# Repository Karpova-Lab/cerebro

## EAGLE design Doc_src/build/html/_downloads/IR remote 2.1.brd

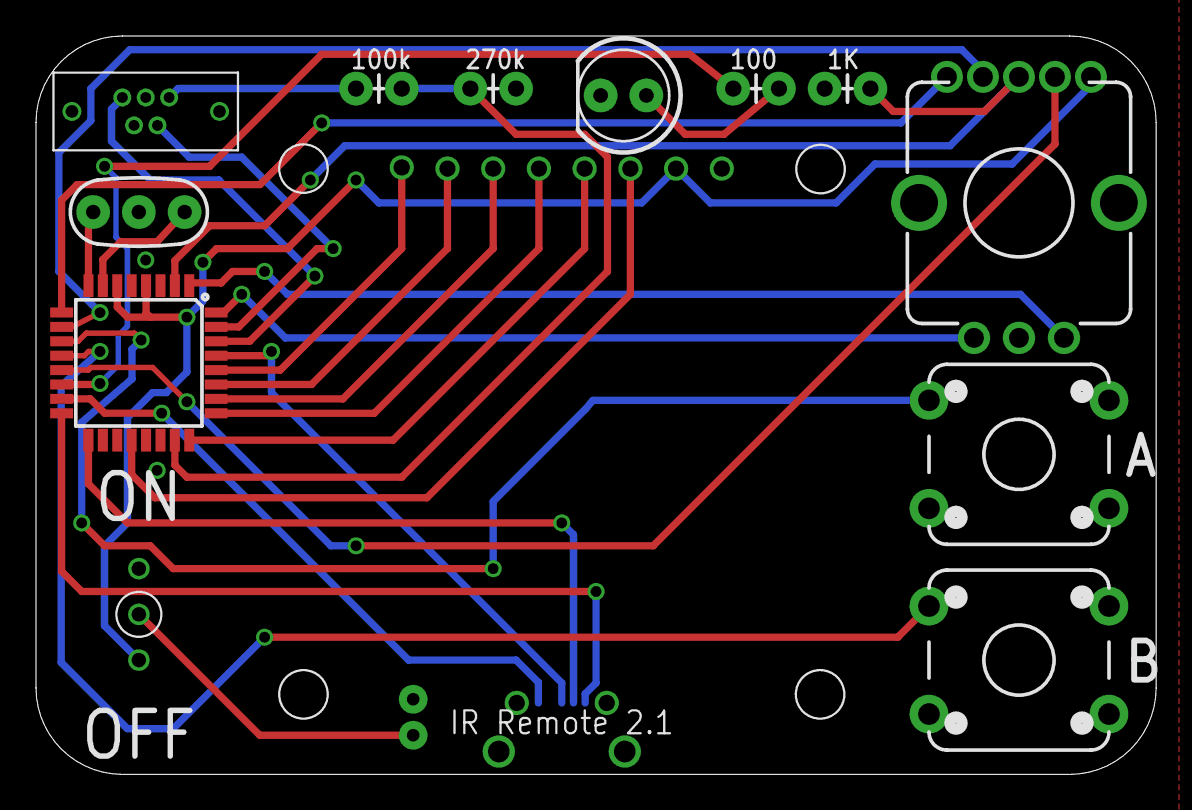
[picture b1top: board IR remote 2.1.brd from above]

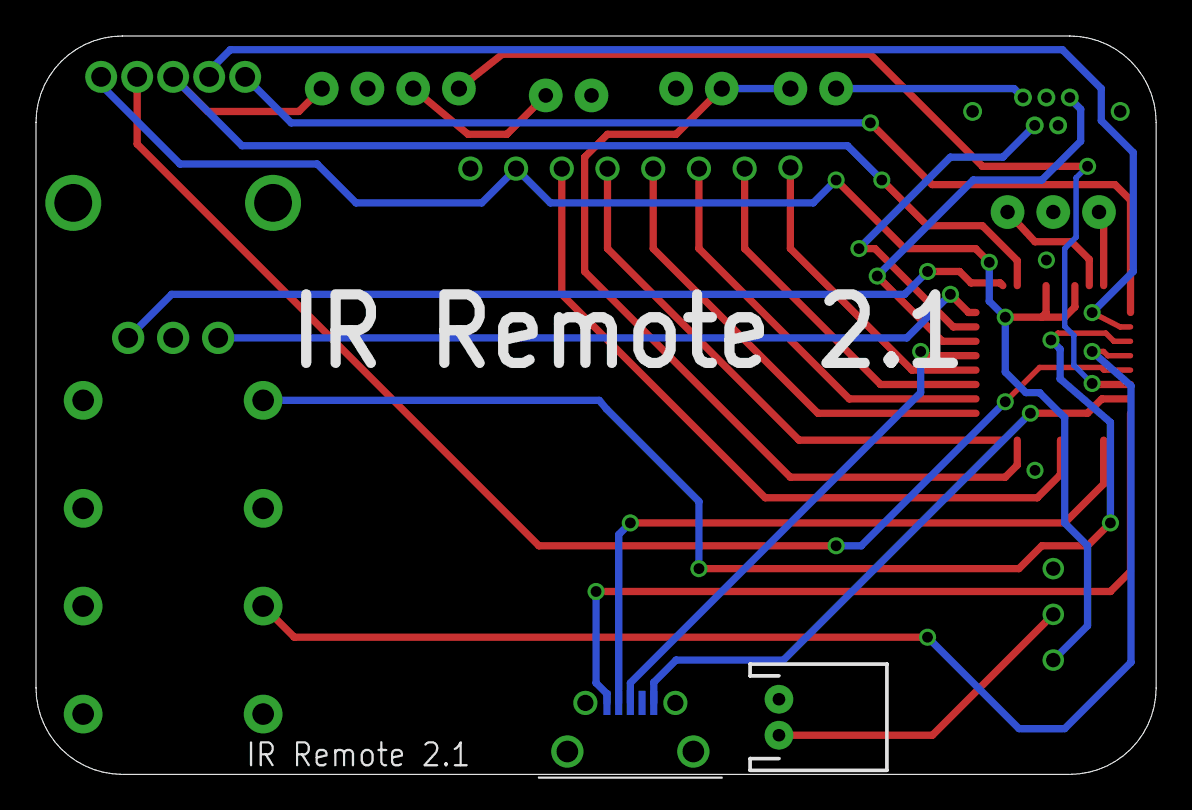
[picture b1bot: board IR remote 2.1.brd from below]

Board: 2 copper layers, 62.2 x 41.0 mm, 15 parts (3 on the bottom side), 29 nets.

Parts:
ICSP_PORT: USB_SOCKET_MICRO_VERTREINFORCED; USB_HORZ_REINFORCED_MICRO
JP1: JST-2-PTH
LED1: LED5MM-KIT
PARAMETER_MONITOR: USB_MICROB_PLUG-PTH2; MICRO-B-TH
R1: 1K; AXIAL-0.1
R2: 270k; AXIAL-0.1
R3: 100k; AXIAL-0.1
R5: 100; AXIAL-0.1
S1, S3: SWITCH-MOMENTARY-2-CLOSED; TACTILE-PTH-12MM
S4: TOGGLE
SW1: ENCODER_LED_3_KIT
U2: ATMEGA328P_TQFP; TQFP32-08
U$1: OLED_DISPLAY
Y1: RESONATOR-PTH

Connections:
3.3VDC: U2.20, U$1.3V3
BATT: JP1.2, S4.P$2
BLUE: SW1.4, U2.13
BTN: R1.P$2, SW1.3, U2.2
GND: ICSP_PORT.G1, ICSP_PORT.G2, ICSP_PORT.P$1, ICSP_PORT.P$2, JP1.1, LED1.K, PARAMETER_MONITOR.P$1, PARAMETER_MONITOR.P$2, R1.P$1, R2.P$1, S1.3, S3.3, SW1.C, U2.3, U2.5, U2.21, U$1.GND, Y1.2
GREEN: SW1.2, U2.10
LED: R5.P$1, U2.14
unnamed: PARAMETER_MONITOR.4, U2.31
unnamed: U2.28, U$1.DATA
unnamed: S1.1, U2.11
unnamed: U2.27, U$1.CLK
unnamed: U2.7, Y1.1
unnamed: U2.8, Y1.3
unnamed: U2.26, U$1.DC
unnamed: U2.25, U$1.RST
unnamed: U2.24, U$1.CS
unnamed: SW1.B, U2.1
unnamed: SW1.A, U2.32
unnamed: PARAMETER_MONITOR.5, R3.P$2
unnamed: LED1.A, R5.P$2
unnamed: PARAMETER_MONITOR.1, U2.30
unnamed: R2.P$2, R3.P$1, U2.23
unnamed: ICSP_PORT.P1, U2.16
unnamed: ICSP_PORT.P2, U2.17
unnamed: ICSP_PORT.P3, U2.29
unnamed: ICSP_PORT.P5, U2.15
unnamed: S3.1, U2.12
RED: SW1.1, U2.9
VIN: S4.P$1, SW1.5, U2.4, U2.6, U$1.VIN

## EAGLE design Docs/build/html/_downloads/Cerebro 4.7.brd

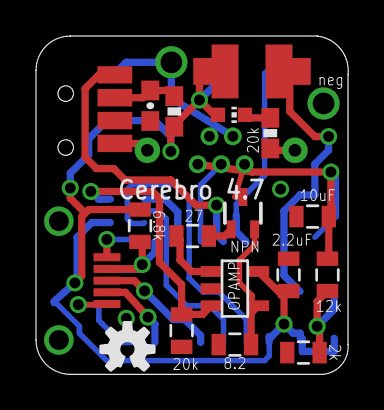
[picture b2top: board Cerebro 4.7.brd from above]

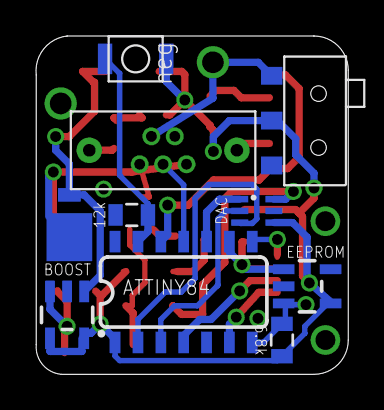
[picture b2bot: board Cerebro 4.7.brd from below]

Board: 2 copper layers, 17.3 x 18.8 mm, 30 parts (9 on the bottom side), 24 nets.

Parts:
C1: .1uF; 0603-CAP
C3: 2.2uF; 0805
C4: 10uF; 0805
D1: MBRM140T3G; POWERMITE
IC1: OPA237N; SOT23-5
INDICATOR_LED: LED; CHIP-LED0603
JP3: USB_MICROB_PLUG-PTH2; MICRO-B-TH
L1: 10uH; 1812
MIC2288: BOOST; SOT23-5
R1: 27; 0805
R2: 8.2; 0805
R3: 2k; 0805
R4, R9: 12k; 0805
R5: 20k; 0603-RES
R6, R7: 6.8k; 0805
R8: 20k; 0805
R10: 100; 0603-RES
S3: SWITCH-SPDT-SMD
SDF: TSOP6238TT; TSOP6
T1: FJX3904TF; SOT323
U$1: DAC_LTC2630; SC-70
U$2: ATTINY84; SO14
U$3: SWITCH-MOMENTARY-NO; SWITCH_MOMENTARY_XS
U$4: EEPROM24C64A; SOT23-5
U$5: USB_SOCKET_MICRO_VERTHORIZONTAL; USB_HORZ_MICRO_SMD
U$6: OSHW-LOGO-S
U$7, U$8: BATT_TERMINAL

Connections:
8.68VDC: C4.1, D1.CATHODE, JP3.1, R4.2
BATT: C3.1, IC1.5, INDICATOR_LED.A, L1.P$2, L1.P$4, MIC2288.4, MIC2288.5, R6.2, R7.2, R10.1, S3.2, U$1.VCC, U$2.1, U$3.P$2, U$4.4
GND: C1.2, C3.2, C4.2, IC1.2, JP3.2, JP3.P$1, JP3.P$2, MIC2288.2, R2.2, R3.1, R5.2, R8.2, R9.1, S3.3, SDF.P$1, SDF.P$2, U$1.GND, U$2.14, U$4.2, U$5.G1, U$5.G2, U$7.P$1
MISO/TX: U$2.8, U$5.P1
MOSI: R7.1, U$2.7, U$4.3, U$5.P5
unnamed: SDF.P$4, U$2.12
unnamed: U$1.CS/LD, U$2.10
unnamed: IC1.3, R8.1, U$1.VOUT
unnamed: JP3.4, S3.1, U$8.P$1
unnamed: JP3.3, U$2.11
unnamed: IC1.4, R2.1, T1.3
unnamed: R9.2, U$2.13, U$3.P$1
unnamed: INDICATOR_LED.C, R5.1
unnamed: IC1.1, R1.2
unnamed: MIC2288.3, R3.2, R4.1
unnamed: R1.1, T1.2
unnamed: C1.1, R10.2, SDF.P$3
unnamed: JP3.5, T1.1
unnamed: U$1.SCK, U$2.3
unnamed: D1.ANODE, L1.P$1, L1.P$3, MIC2288.1
unnamed: U$1.SDI, U$2.2
RESET: U$2.4, U$5.P3
RX: U$2.6, U$5.P4
SCK: R6.1, U$2.9, U$4.1, U$5.P2

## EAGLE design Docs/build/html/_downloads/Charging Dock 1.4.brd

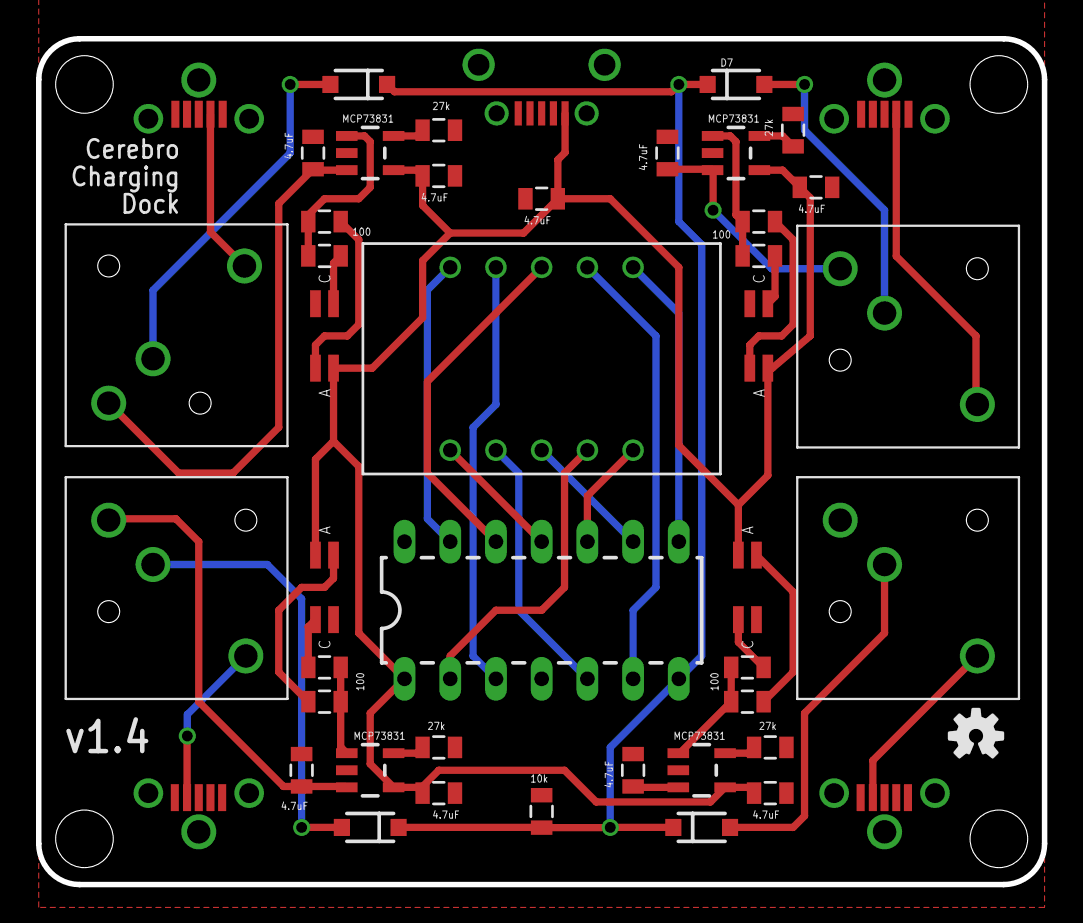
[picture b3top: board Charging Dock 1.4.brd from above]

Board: 2 copper layers, 55.9 x 47.0 mm, 47 parts (1 on the bottom side), 41 nets.

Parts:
C2, C3, C4, C5, C6, C7, C8, C10, C11: 4.7uF; 0805
D5, D6, D7, D8: SOD-123
DIS1: HD-A1032DIGIT; HDSP-A
R1, R2, R4, R5, R7, R8, R14, R15: 100; 0805
R3, R6, R9, R16: 27k; 0805
R10: 10k; 0805
U1, U2, U3, U5: MCP73831; SOT23-5
U$1, U$3, U$4, U$5: SPDT_MOMENTARY; SPDT_MOMENTRAY
U$2: ATTINY84ATTINY84-20PU; DIL14
U$6, U$7, U$8, U$9: USB_SOCKET_MICRO_VERT; USB_VERT_MICRO_SMD
U$11, U$12, U$13, U$14: LED_DUAL
U$15: OSHW-LOGO-M
U$16: OSHW-LOGO-S
U$17: USB_SOCKET_MICRO_VERTREINFORCED; USB_HORZ_REINFORCED_MICRO

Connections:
5VDC: C3.1, C5.1, C7.1, C8.2, C11.1, U1.4, U2.4, U3.4, U5.4, U$2.1, U$11.RA, U$12.RA, U$13.RA, U$14.RA, U$17.P1
GND: C2.2, C3.2, C4.2, C5.2, C6.2, C7.2, C8.1, C10.2, C11.2, R3.2, R6.2, R9.2, R10.2, R16.2, U1.2, U2.2, U3.2, U5.2, U$2.14, U$6.P4, U$7.P4, U$8.P4, U$9.P4, U$11.GC, U$12.GC, U$13.GC, U$14.GC, U$17.G1, U$17.G2, U$17.P5, U$17.P$1, U$17.P$2
unnamed: DIS1.10, U$2.13
unnamed: R3.1, U1.5
unnamed: C2.1, U1.3, U$5.1
unnamed: R1.2, R2.2, U1.1
unnamed: R1.1, U$12.GA
unnamed: R2.1, U$12.RC
unnamed: R6.1, U2.5
unnamed: C4.1, U2.3, U$4.1
unnamed: R4.2, R5.2, U2.1
unnamed: R4.1, U$13.GA
unnamed: U$5.COMMON, U$6.P2
unnamed: R5.1, U$13.RC
unnamed: R9.1, U3.5
unnamed: C6.1, U3.3
unnamed: R7.2, R8.2, U3.1
unnamed: R7.1, U$14.GA
unnamed: U$3.COMMON, U$9.P2
unnamed: R8.1, U$14.RC
unnamed: DIS1.8, U$2.12
unnamed: DIS1.1, U$2.11
unnamed: DIS1.5, U$2.10
unnamed: DIS1.3, U$2.9
unnamed: DIS1.6, U$2.8
unnamed: DIS1.7, U$2.6
unnamed: DIS1.9, U$2.3
unnamed: DIS1.2, U$2.5
unnamed: DIS1.4, U$2.2
unnamed: D6.A, U$3.2
unnamed: U$4.COMMON, U$8.P2
unnamed: D8.A, U$4.2
unnamed: U$1.COMMON, U$7.P2
unnamed: D5.A, U$1.2
unnamed: D5.C, D6.C, D7.C, D8.C, R10.1, U$2.7
unnamed: D7.A, U$5.2
unnamed: R16.1, U5.5
unnamed: C10.1, U5.3, U$1.1
unnamed: R14.2, R15.2, U5.1
unnamed: R14.1, U$11.GA
unnamed: R15.1, U$11.RC

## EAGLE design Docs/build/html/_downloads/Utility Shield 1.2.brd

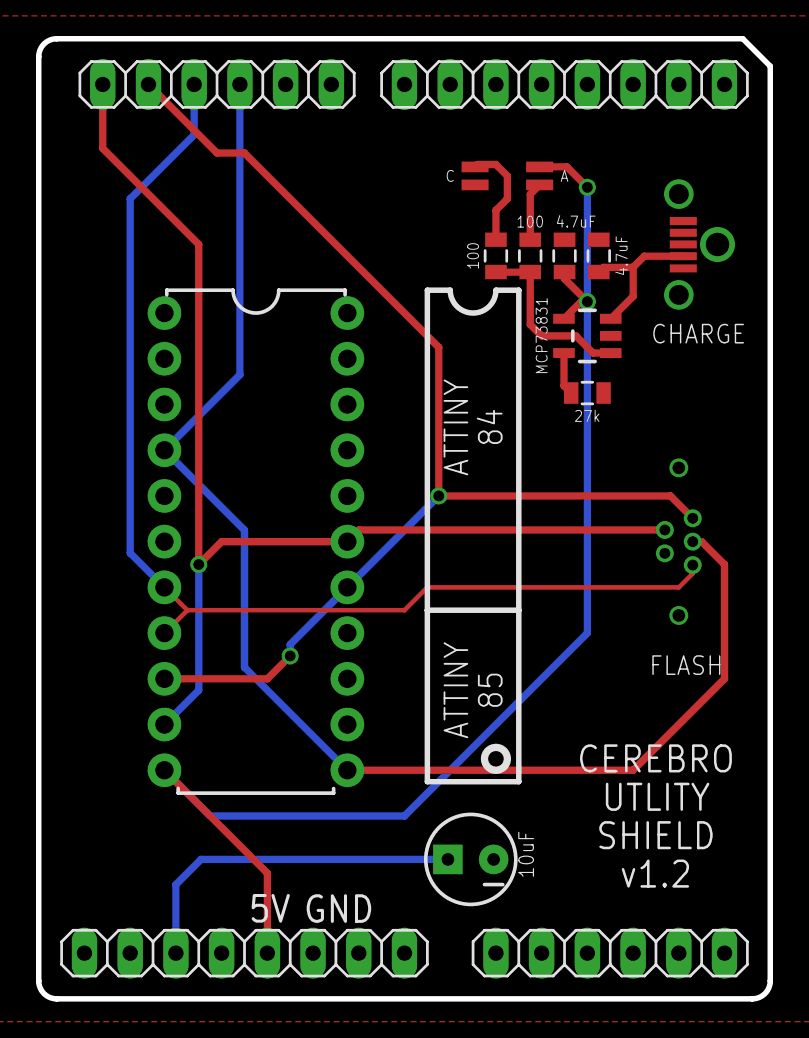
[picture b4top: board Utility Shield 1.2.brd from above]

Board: 2 copper layers, 40.6 x 53.3 mm, 15 parts (0 on the bottom side), 12 nets.

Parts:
AD, AD1: 6x1F-H8.5; 1X06
C1: 10uF; CPOL-RADIAL-10UF-25V
C2, C3: 4.7uF; 0805
IOL: 8x1F-H8.5; 1X08
JP1: USB_MICROB_PLUG-PTH2; MICRO-B-TH
POWER: 8x1F-H8.5; 1X08
R1, R2: 100; 0805
R3: 27k; 0805
U2: MCP73831; SOT23-5
U$1: ZIF_22
U$2: LED_DUAL
U$3: USB_SOCKET_MICRO_VERT; USB_VERT_MICRO_SMD

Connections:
5VDC: C3.1, POWER.5, U2.4, U$1.11, U$2.RA
GND: C1.2, C2.2, C3.2, JP1.4, JP1.P$1, JP1.P$2, POWER.6, POWER.7, R3.2, U2.2, U$1.15, U$1.22, U$2.GC, U$3.P4, U$3.P$1, U$3.P$2, U$3.P$3
MISO: AD1.5, JP1.1, U$1.9, U$1.16
MOSI: AD1.4, JP1.5, U$1.7, U$1.8
unnamed: C1.1, POWER.3
unnamed: R1.2, R2.2, U2.1
unnamed: R1.1, U$2.GA
unnamed: R2.1, U$2.RC
unnamed: R3.1, U2.5
unnamed: C2.1, U2.3, U$3.P2
RST: AD1.3, JP1.3, U$1.4, U$1.12
SCK: AD1.6, JP1.2, U$1.10, U$1.17

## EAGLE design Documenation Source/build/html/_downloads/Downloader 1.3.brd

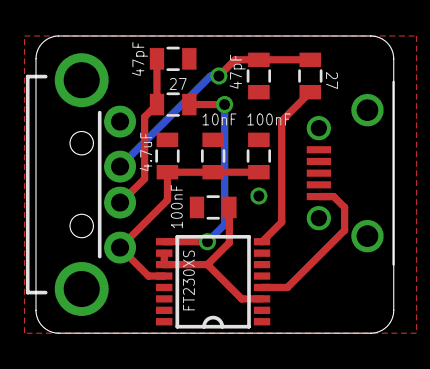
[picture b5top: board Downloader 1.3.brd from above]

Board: 2 copper layers, 19.9 x 16.5 mm, 12 parts (1 on the bottom side), 8 nets.

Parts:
C1, C10: 100nF; 0805
C3: 10nF; 0805
C4: 4.7uF; 0805
C7, C8: 47pF; 0805
IC1: FT230XS; SSOP16
JP1: USB-A-H
R1, R2: 27; 0805
U$1: USB_SOCKET_MICRO_VERTREINFORCED; USB_HORZ_REINFORCED_MICRO
U$2: OSHW-LOGO-M

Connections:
5VDC: C1.2, C3.2, C4.2, IC1.12, JP1.VBUS
84_TX: IC1.4, U$1.P1
D+: C8.2, JP1.D+, R2.2
GND: C1.1, C3.1, C4.1, C7.2, C8.1, C10.1, IC1.5, IC1.13, JP1.GND, JP1.GND2, JP1.GND3, U$1.G1, U$1.G2, U$1.P$1, U$1.P$2
unnamed: C7.1, JP1.D-, R1.2
unnamed: IC1.9, R1.1
unnamed: C10.2, IC1.3, IC1.10, IC1.11
unnamed: IC1.8, R2.1

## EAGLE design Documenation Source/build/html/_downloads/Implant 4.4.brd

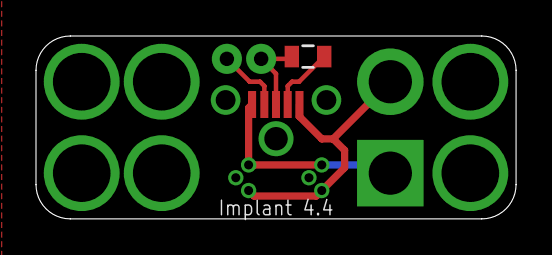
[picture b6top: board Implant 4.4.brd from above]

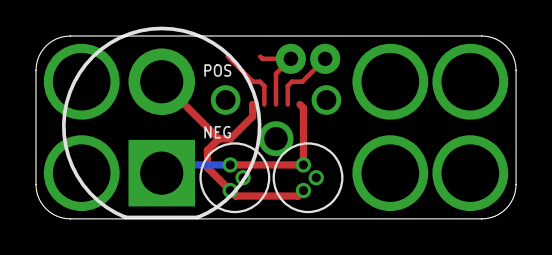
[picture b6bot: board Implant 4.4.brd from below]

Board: 2 copper layers, 26.7 x 10.2 mm, 6 parts (3 on the bottom side), 6 nets.

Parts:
JP1: M02SMALL; 1X02_SMALL
LED1: LED10MM
R2: 6.8k; 0805
U$1, U$3: LASERDIODE
U$2: USB_SOCKET_MICRO_VERT; USB_VERT_MICRO_SMD

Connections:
HEATSINK: U$1.P$3, U$3.P$3
LD+: LED1.A, U$1.P$1, U$2.P5, U$3.P$1
LD-: LED1.C, U$1.P$2, U$2.P1, U$3.P$2
unnamed: R2.1, U$2.P4
unnamed: JP1.P$2, U$2.P2
unnamed: JP1.P$1, R2.2, U$2.P3

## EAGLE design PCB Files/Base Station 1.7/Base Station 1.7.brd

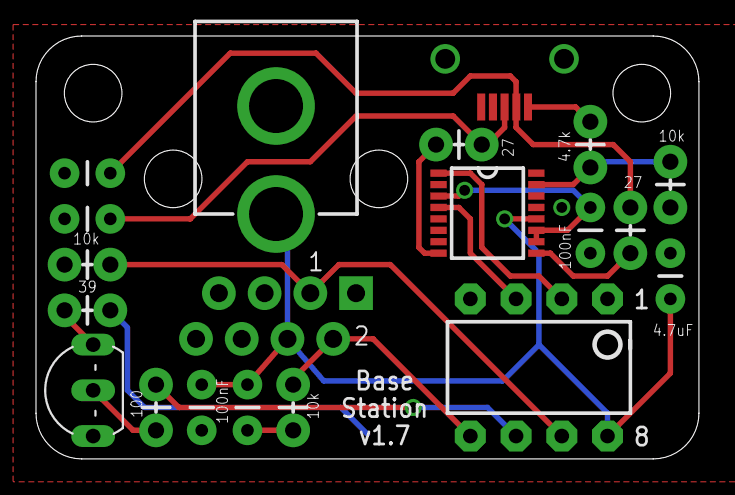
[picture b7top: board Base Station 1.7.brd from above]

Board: 2 copper layers, 36.8 x 23.5 mm, 21 parts (1 on the bottom side), 17 nets.

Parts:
C1, C2: 47pF; CAP-PTH-SMALL
C5, C6, C7: 100nF; CAP-PTH-SMALL
C8: 4.7uF; CAP-PTH-SMALL
IC1: FT230XS; SSOP16
J1: POWER_JACKPTH; POWER_JACK_PTH
LED1: PLCC-2
Q1: 2222A; TO92-EBC-OVAL
R1: 39; AXIAL-0.1
R2: 100; AXIAL-0.1
R3, R5, R15: 10k; AXIAL-0.1
R13, R16: 27; AXIAL-0.1
R14: 4.7k; AXIAL-0.1
U2: TINY85-20-DIP; DIP08
U$1: USB_SOCKET_MICRO_VERTHORIZONTAL; USB_HORZ_MICRO_SMD
U$3: RJ45; RJ45-8

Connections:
5VDC: C5.1, C6.1, C8.1, IC1.12, J1.PWR, LED1.ANODE, U2.8, U$3.4
85_RX: IC1.1, U2.2
85_TX: IC1.4, U2.3
GND: C1.1, C2.2, C5.2, C6.2, C7.2, C8.2, IC1.5, IC1.13, J1.GND, Q1.E, R3.P$2, R5.P$2, R15.P$1, U2.4, U$1.G1, U$1.G2, U$1.P5, U$3.5
unnamed: Q1.C, R1.P$1
unnamed: LED1.CATHODE, R1.P$2
unnamed: R2.P$1, U2.6
unnamed: Q1.B, R2.P$2
unnamed: C1.2, R16.P$1, U$1.P2
unnamed: C2.1, R13.P$2, U$1.P3
unnamed: R14.P$2, U$1.P1
unnamed: IC1.9, R16.P$2
unnamed: C7.1, IC1.3, IC1.10, IC1.11
unnamed: IC1.15, R14.P$1, R15.P$2
unnamed: IC1.8, R13.P$1
OUT1: R3.P$1, U2.7, U$3.3
OUT2: R5.P$1, U2.5, U$3.2

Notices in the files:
parts and their libraries:
SparkFun-DigitalIC: Licensing: Creative Commons ShareAlike 4.0 International - https://creativecommons.org/licenses/by-sa/4.0
